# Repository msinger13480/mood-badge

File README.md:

# mood-badge
Part of the 2021 Milestones Intro to Electronics Pro workshop

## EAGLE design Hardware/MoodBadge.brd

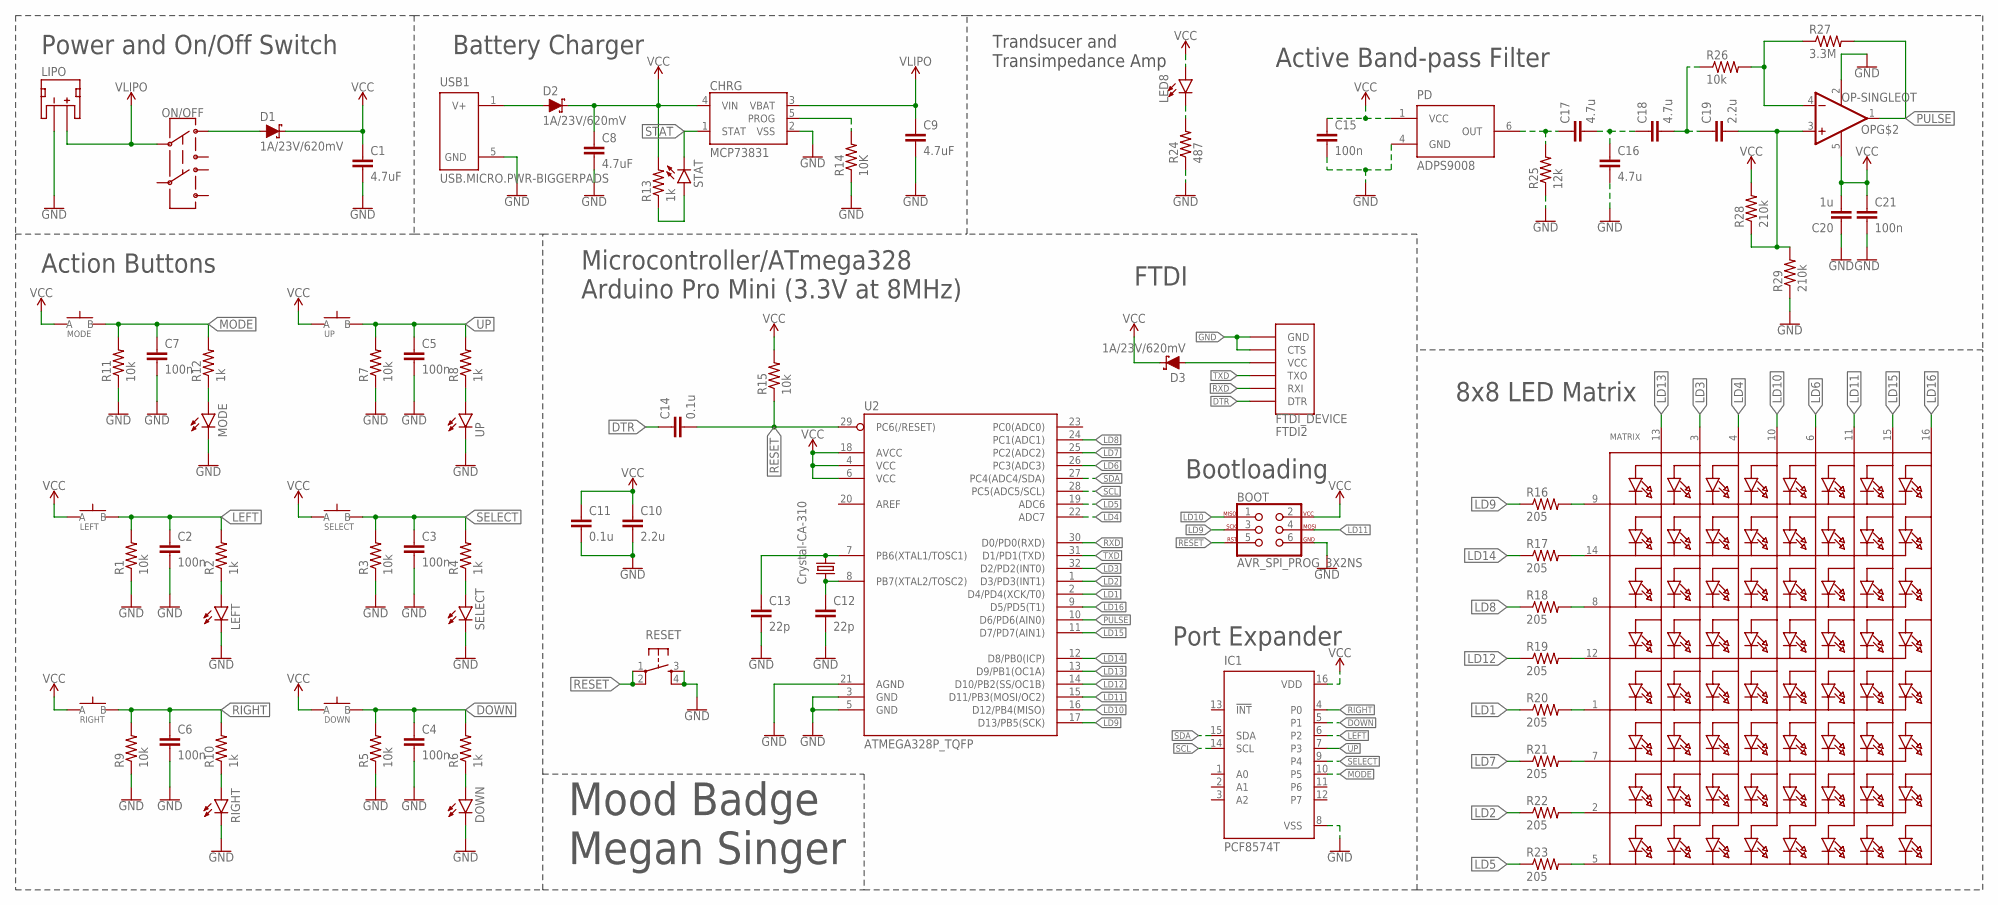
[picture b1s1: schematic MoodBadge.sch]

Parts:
BOOT: AVR_SPI_PROG_3X2NS; 2X3-NS
C1, C8, C9: 4.7uF; 0603
C2, C3, C4, C5, C6, C7: 100n; C0603
C10: 2.2u; C0603
C11, C14: 0.1u; C0603
C12, C13: 22p; C0603
C15, C21: 100n; 0603
C16, C17, C18: 4.7u; 0603
C19: 2.2u; 0603
C20: 1u; 0603
CHRG: MCP73831; SOT23-5
D1, D2, D3: 1A/23V/620mV; USC
DOWN: SPST.KT11P4SM34LFS
FTDI2: FTDI_DEVICE
IC1: PCF8574T; SO16W
LED1: LEFT; LED-0603
LED2: SELECT; LED-0603
LED3: DOWN; LED-0603
LED4: UP; LED-0603
LED5: RIGHT; LED-0603
LED6: MODE; LED-0603
LED7: STAT; LED-0603
LED8: LEDZ-BEND; 2-SMD.Z-BEND
LEFT: SPST.KT11P4SM34LFS
LIPO: JST_2MM_MALE; JST-2-SMD
MATRIX: SEGMENT_8X8_ROWCATHODEBL-M12A883; SEGMENT_BL-M12A883
MODE: SPST.KT11P4SM34LFS
ON/OFF: SWITCH.JS202011JXQNUPWARDS; SWITCH.00
OP: OP-SINGLEOT; SOT23-5
PD: ADPS9008; 6-PIN.CHIPLED
R1, R3, R5, R7, R9, R11, R15, R26: 10k; R0603
R2, R4, R6, R8, R10, R12, R13: 1k; R0603
R14: 10K; R0603
R16, R17, R18, R19, R20, R21, R22, R23: 205; R0603
R24: 487; R0603
R25: 12k; R0603
R27: 3.3M; R0603
R28, R29: 210k; R0603
RESET: SPST-PTS830GG140; BUTTON-GULLWING
RIGHT: SPST.KT11P4SM34LFS
SELECT: SPST.KT11P4SM34LFS
U2: ATMEGA328P_TQFP; TQFP32-08
UP: SPST.KT11P4SM34LFS
USB1: USB.MICRO.PWR-BIGGERPADS; USB-MICRO-01.BIGGERPADS.PWR
Y1: Crystal-CA-310; CA-301

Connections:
DOWN: C4.1, DOWN.3 (B), DOWN.4 (B), IC1.5 (P1), R5.2, R6.2
DTR: C14.1, FTDI2.DTR
GND: BOOT.6, C1.2, C2.2, C3.2, C4.2, C5.2, C6.2, C7.2, C8.2, C9.2, C10.2, C11.2, C12.2, C13.2, C15.2, C16.2, C20.1, C21.2, CHRG.2 (VSS), FTDI2.CTS, FTDI2.GND, IC1.8 (VSS), LED1.C, LED2.C, LED3.C, LED4.C, LED5.C, LED6.C, LIPO.1 (-), OP.2 (V-), PD.4 (GND), R1.1, R3.1, R5.1, R7.1, R9.1, R11.1, R14.1, R24.1, R25.1, R29.1, RESET.3, RESET.4, U2.3 (GND), U2.5 (GND), U2.21 (AGND), USB1.5 (GND)
LD1: R20.1, U2.2 (D4/PD4(XCK/T0))
LD2: R22.1, U2.1 (D3/PD3(INT1))
LD3: MATRIX.3 (A2), U2.32 (D2/PD2(INT0))
LD4: MATRIX.4 (A3), U2.22 (ADC7)
LD5: R23.1, U2.19 (ADC6)
LD6: MATRIX.6 (A5), U2.26 (PC3(ADC3))
LD7: R21.1, U2.25 (PC2(ADC2))
LD8: R18.1, U2.24 (PC1(ADC1))
LD9: BOOT.3, R16.1, U2.17 (D13/PB5(SCK))
LD10: BOOT.1, MATRIX.10 (A4), U2.16 (D12/PB4(MISO))
LD11: BOOT.4, MATRIX.11 (A6), U2.15 (D11/PB3(MOSI/OC2))
LD12: R19.1, U2.14 (D10/PB2(SS/OC1B))
LD13: MATRIX.13 (A1), U2.13 (D9/PB1(OC1A))
LD14: R17.1, U2.12 (D8/PB0(ICP))
LD15: MATRIX.15 (A7), U2.11 (D7/PD7(AIN1))
LD16: MATRIX.16 (A8), U2.9 (D5/PD5(T1))
LEFT: C2.1, IC1.6 (P2), LEFT.3 (B), LEFT.4 (B), R1.2, R2.2
MODE: C7.1, IC1.10 (P5), MODE.3 (B), MODE.4 (B), R11.2, R12.2
unnamed: D2.+ (A), USB1.1 (V+)
unnamed: D1.+ (A), ON/OFF.1
unnamed: LED1.A, R2.1
unnamed: CHRG.5 (PROG), R14.2
unnamed: LED2.A, R4.1
unnamed: LED7.A, R13.1
unnamed: LED3.A, R6.1
unnamed: C13.1, U2.7 (PB6(XTAL1/TOSC1)), Y1.2
unnamed: LED4.A, R8.1
unnamed: C12.1, U2.8 (PB7(XTAL2/TOSC2)), Y1.1
unnamed: LED5.A, R10.1
unnamed: D3.+ (A), FTDI2.VCC
unnamed: LED6.A, R12.1
unnamed: MATRIX.9 (K1), R16.2
unnamed: MATRIX.14 (K2), R17.2
unnamed: MATRIX.8 (K3), R18.2
unnamed: MATRIX.12 (K4), R19.2
unnamed: MATRIX.1 (K5), R20.2
unnamed: MATRIX.7 (K6), R21.2
unnamed: MATRIX.2 (K7), R22.2
unnamed: MATRIX.5 (K8), R23.2
unnamed: LED8.- (C), R24.2
unnamed: C17.1, PD.6 (OUT), R25.2
unnamed: C16.1, C17.2, C18.1
unnamed: C19.2, OP.3 (+IN), R28.1, R29.2
unnamed: C18.2, C19.1, R26.1
unnamed: OP.4 (-IN), R26.2, R27.1
PULSE: OP.1 (OUT), R27.2, U2.10 (D6/PD6(AIN0))
RESET: BOOT.5, C14.2, R15.1, RESET.1, RESET.2, U2.29 (PC6(/RESET))
RIGHT: C6.1, IC1.4 (P0), R9.2, R10.2, RIGHT.3 (B), RIGHT.4 (B)
RXD: FTDI2.TXO (RXI), U2.30 (D0/PD0(RXD))
SCL: IC1.14 (SCL), U2.28 (PC5(ADC5/SCL))
SDA: IC1.15 (SDA), U2.27 (PC4(ADC4/SDA))
SELECT: C3.1, IC1.9 (P4), R3.2, R4.2, SELECT.3 (B), SELECT.4 (B)
STAT: CHRG.1 (STAT), LED7.C
TXD: FTDI2.RXI (TXO), U2.31 (D1/PD1(TXD))
UP: C5.1, IC1.7 (P3), R7.2, R8.2, UP.3 (B), UP.4 (B)
VCC: BOOT.2, C8.1, C10.1, C11.1, C15.1, C20.2, C21.1, CHRG.4 (VIN), D2.- (C), D3.- (C), DOWN.1 (A), DOWN.2 (A), IC1.16 (VDD), LED8.+ (A), LEFT.1 (A), LEFT.2 (A), MODE.1 (A), MODE.2 (A), OP.5 (V+), PD.1 (VCC), R13.2, R15.2, R28.2, RIGHT.1 (A), RIGHT.2 (A), SELECT.1 (A), SELECT.2 (A), U2.4 (VCC), U2.6 (VCC), U2.18 (AVCC), UP.1 (A), UP.2 (A)
VLIPO: C1.1, C9.1, CHRG.3 (VBAT), D1.- (C), LIPO.2 (+), ON/OFF.2

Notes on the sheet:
Power and On/Off Switch
Action Buttons
Battery Charger
Microcontroller/ATmega328 Arduino Pro Mini (3.3V at 8MHz)
FTDI
Bootloading
8x8 LED Matrix
Trandsucer and Transimpedance Amp
Active Band-pass Filter
Port Expander
Mood Badge Megan Singer

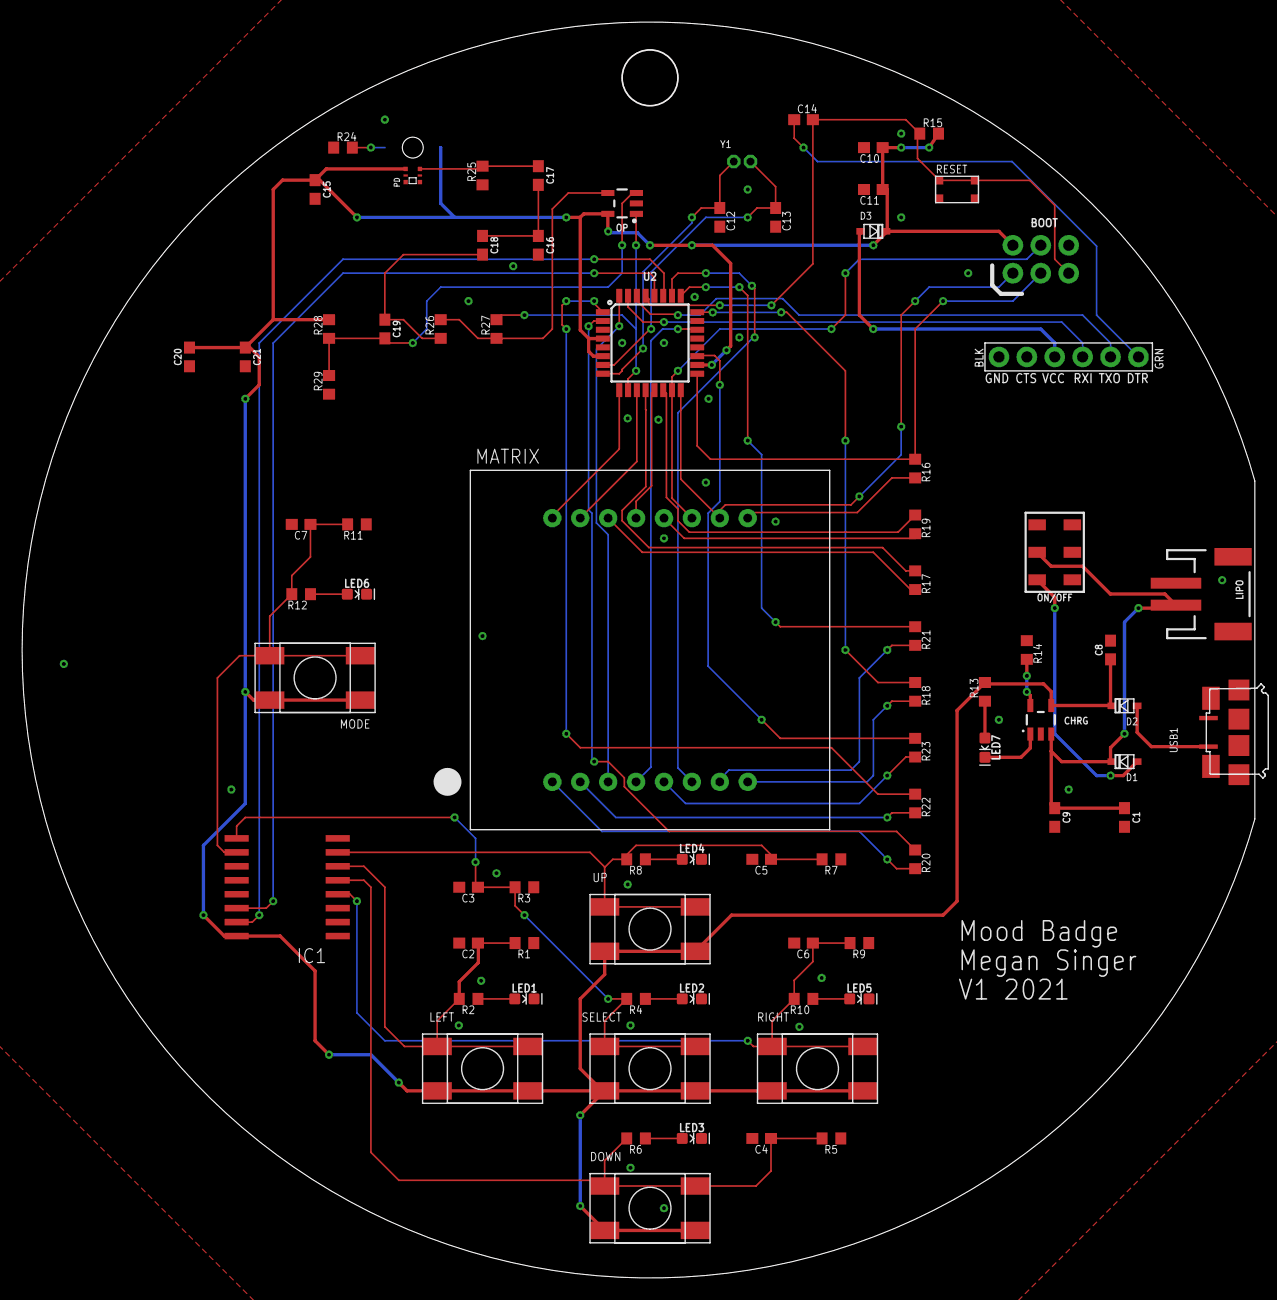
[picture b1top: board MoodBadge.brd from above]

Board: 2 copper layers, 112.1 x 114.2 mm, 80 parts (1 on the bottom side), 60 nets.

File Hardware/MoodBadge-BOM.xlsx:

Mood Badge -- V1 / Megan Singer |  |  |  |  |  |  |  |  |  |  | Total | 2.48 | Total (in Bulk) | 1.1271
BOM # | Comment | Designator | Description | Mounting Type | Package | Manufacturer | Manufacturer Part Number | Supplier | Supplier Part Number | Price per unit | Quantity | Total | Per 100 | Total
1 | LM358 | OP1 | General Purpose Amplifier 2 Circuit 8-SOIC | SMD | 8-SOIC | Texas Instruments | LM358DR | Digi-Key | 296-1014-1-ND | 0.38 | 1 | 0.38 | 0.1391 | 0.1391
2 | Photoresistor | Photo | CDS Cell 520nm 27 ~ 60kOhms @ 10 lux | THT | Radial | Advanced Photonix | PDV-P8104 | Digi-Key | PDV-P8104-ND | 0.89 | 1 | 0.89 | 0.46 | 0.46
3 | 9V Battery Connector | 9V | Battery Connector, Snap 9V 1 Cell Wire Leads - 4" (101.6mm) | THT |  | Keystone Electronics | 81-4 | Digi-Key | 36-81-4-ND | 0.55000000000000004 | 1 | 0.55000000000000004 | 0.3982 | 0.3982
4 | White LED | LED1 | White LED Indication - Discrete 2.9V Radial | THT | Radial | American Bright Optoelectronics Corporation | BL-BZX3V4V-1-B02 | Digi-Key | BL-BZX3V4V-1-B02-ND | 0.26 | 1 | 0.26 | 9.0899999999999995E-2 | 9.0899999999999995E-2
5 | 10k resistor | R1,R2,R3 | 10 kOhms ±1% 0.1W, 1/10W Chip Resistor 0603 (1608 Metric) Automotive AEC-Q200 T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 | SMD | 0603 | Stackpole Electronics Inc | RMCF0603FT10K0 | Digi-Key | RMCF0603FT10K0CT-ND | 0.1 | 3 | 0.30000000000000004 | 6.7999999999999996E-3 | 2.0399999999999998E-2
6 | 1uF capacitor | C1 | 1µF ±10% 25V Ceramic Capacitor X5R 0603 (1608 Metric) | SMD | 0603 | Samsung Electro-Mechanics | CL10A105KA8NNNC | Digi-Key | 1276-1102-1-ND | 0.1 | 1 | 0.1 | 1.8499999999999999E-2 | 1.8499999999999999E-2
 | 100 nF capacitor | C2, C3, C4, C5, C6, C7, C15, C21 |  | SMD | 0603
 | 4.7 uF capacitor | C1, C8, C9, C16, C17, C18, |  | SMD | 0603
 | 2.2 uF capacitor | C10, C19 |  | SMD | 0603
 | 1 uF capacitor | C20 |  | SMD | 0603
 | 0.1 uF capacitor | C11, C14 |  | SMD | 0603
 | 22 pF capacitor | C12, C13 |  | SMD | 0603
 | 205 ohm resistor | R16, R17, R18, R19, R20, R21, R22, R23 |  | SMD | 0603
 | 487 ohm resistor | R24 |  | SMD | 0603
 | 1 kohm resistor | R2, R4, R6, R8, R10, R12, R13 |  | SMD | 0603
 | 10 kohm resistor | R1, R3, R5, R7, R9, R11, R14, R15, R26 |  | SMD | 0603
 | 12 kohm resistor | R25 |  | SMD | 0603
 | 210 kohm resistor | R28, R29 |  | SMD | 0603
 | 3.3 Mohm resistor | R27 |  | SMD | 0603
 | Clock crystal | Y1 |  | THT |  |  | CA-310
 | Diode | D1, D2, D3 |  | SMD | 0603
 | IR LED | LED8
 | LED | LED1, LED2, LED3, LED4, LED5, LED6, LED7 |  | SMD | 0603
 | LED matrix | MATRIX |  | THT |  | Adafruit Industries | SEGMENT_8X8_ROWCATHODEBL-M12A883
 | Large push button | UP, DOWN, LEFT, RIGHT, SELECT, MODE |  | SMD |  |  | SPST.KT11P4SM34LFS
 | Small push button | RESET |  | SMD |  |  | SPST-PTS830GG140
 | Switch | ON/OFF |  | SMD |  |  | SWITCH.JS202011JXQNUPWARDS
 | Bootloader 2x3 pins | BOOT |  | THT
 | FTDI 1x6 pins | FTDI_DEVICE |  | THT
 | USB port | USB1 |  | SMD
 | LIPO battery port | LIPO |  | SMD
 | Battery charger IC | CHRG |  | SMD |  |  | MCP73831
 | Port expander | IC1 |  | SMD | SO16W |  | PCF8574T
 | Arduino ATMEGA328 | U2 |  | SMD | QFP
 | Op amp | OP |  | SMD | SOT23-5
 | Transducer | PD |  | SMD | APDS9008

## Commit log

2021-02-20 features list
2021-02-20 bill of materials
2021-02-20 updated BOM file name
2021-02-27 EAGLE files
2021-02-27 updated BOM file location
2021-02-27 changed file location
2021-02-27 Updated features list
2021-02-27 added custom emojis and games
2021-02-27 more details on modes and components
2021-02-27 sketch of initial design
2021-03-06 Created board outline and started schematic
2021-03-13 Added battery charger and microcontroller sections
2021-03-13 Added LED matrix and fixed Arduino output pins
2021-03-13 Added remaining parts of circuit and port expander. Connected Pulse pin
2021-03-13 Fixed incorrect values and made organizational adjustments
2021-03-13 Added title block
2021-03-13 Placed the matrix and the direction buttons
2021-03-13 Initial placement of components
2021-03-20 Began routing traces and added flat edge to board outline
2021-03-20 Continued routing and changed a few pins for easier routing
2021-03-20 Edited copper pour outline for easier visibility
2021-03-27 Finished creating traces and filled copper pour
2021-03-27 Adjusted trace width and ran DRC
2021-03-27 Fixed labeling error for FTDI pins
2021-03-27 Added ground plane vias
2021-03-27 Finished adding ground plane vias
2021-03-27 Changed heart rate LED to IR LED and moved closer to the photoresistor
2021-03-27 Listed all part names and designators
2021-04-03 Completed a majority of the BOM. Missing 5 components

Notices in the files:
parts and their libraries:
SparkFun-Capacitors: Licensing: Creative Commons ShareAlike 4.0 International - https://creativecommons.org/licenses/by-sa/4.0
